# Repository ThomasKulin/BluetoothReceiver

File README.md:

# BluetoothReceiver
TODO:
make this readme not shit

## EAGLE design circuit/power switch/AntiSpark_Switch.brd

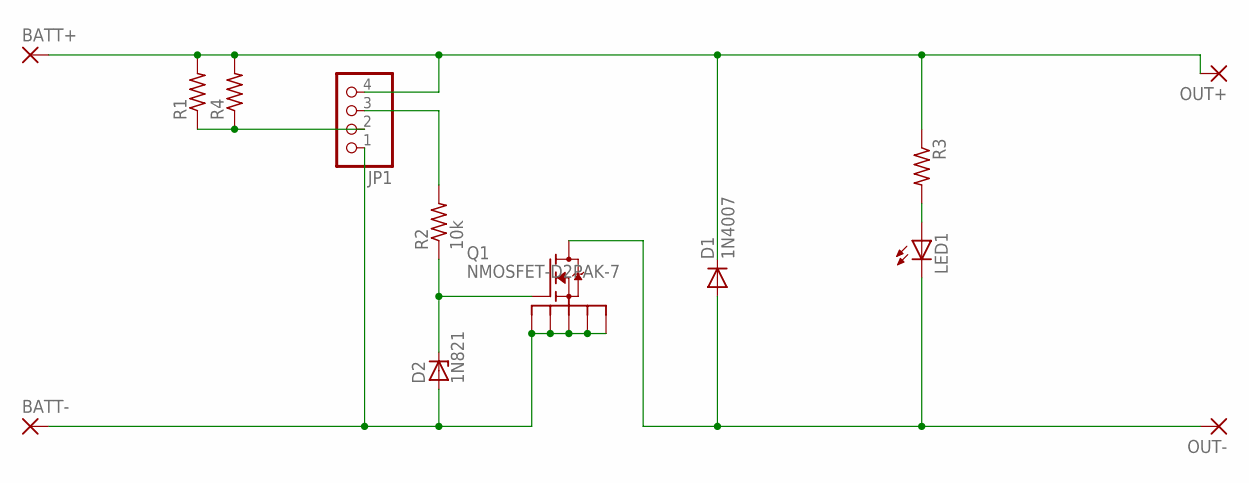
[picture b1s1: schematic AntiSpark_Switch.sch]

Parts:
BATT+: WIREPAD4,16O1,6; 4,16O1,6
BATT-: WIREPAD4,16O1,6; 4,16O1,6
D1: 1N4007; DO41-10
D2: 1N821; DO35Z10
JP1: PINHD-1X4; 1X04
LED1: LED5MM
OUT+: WIREPAD4,16O1,6; 4,16O1,6
OUT-: WIREPAD4,16O1,6; 4,16O1,6
Q1: NMOSFET-D2PAK-7; D2PAK-7
R1, R3, R4: R-US_0207/7; 0207/7
R2: 10k; 0207/7

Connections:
unnamed: BATT-.1, D2.A, JP1.1, Q1.S1, Q1.S2, Q1.S3, Q1.S4, Q1.S5
unnamed: D2.C, Q1.G, R2.1
unnamed: JP1.3, R2.2
unnamed: BATT+.1, D1.C, JP1.4, OUT+.1, R1.2, R3.1, R4.2
unnamed: D1.A, LED1.K (C), OUT-.1, Q1.D
unnamed: JP1.2, R1.1, R4.1
unnamed: LED1.A, R3.2

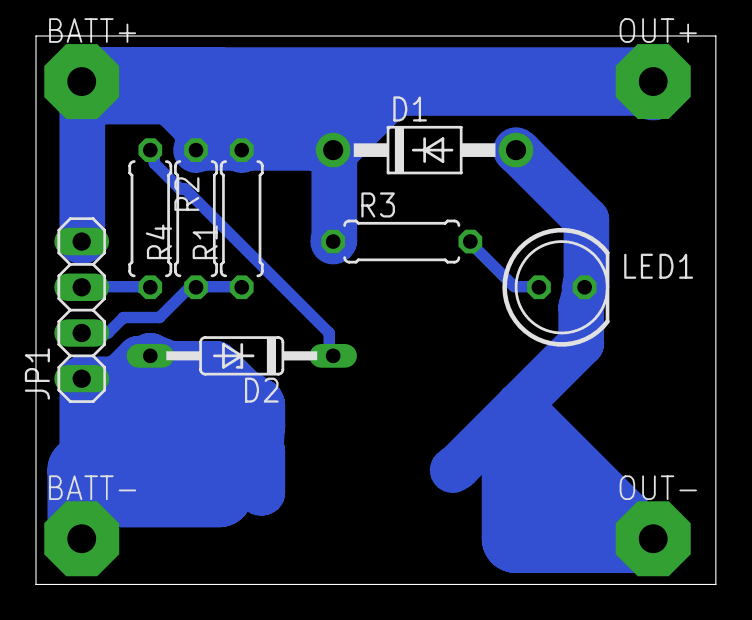
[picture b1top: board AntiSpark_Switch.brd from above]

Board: 2 copper layers, 37.8 x 30.5 mm, 13 parts (1 on the bottom side), 7 nets.

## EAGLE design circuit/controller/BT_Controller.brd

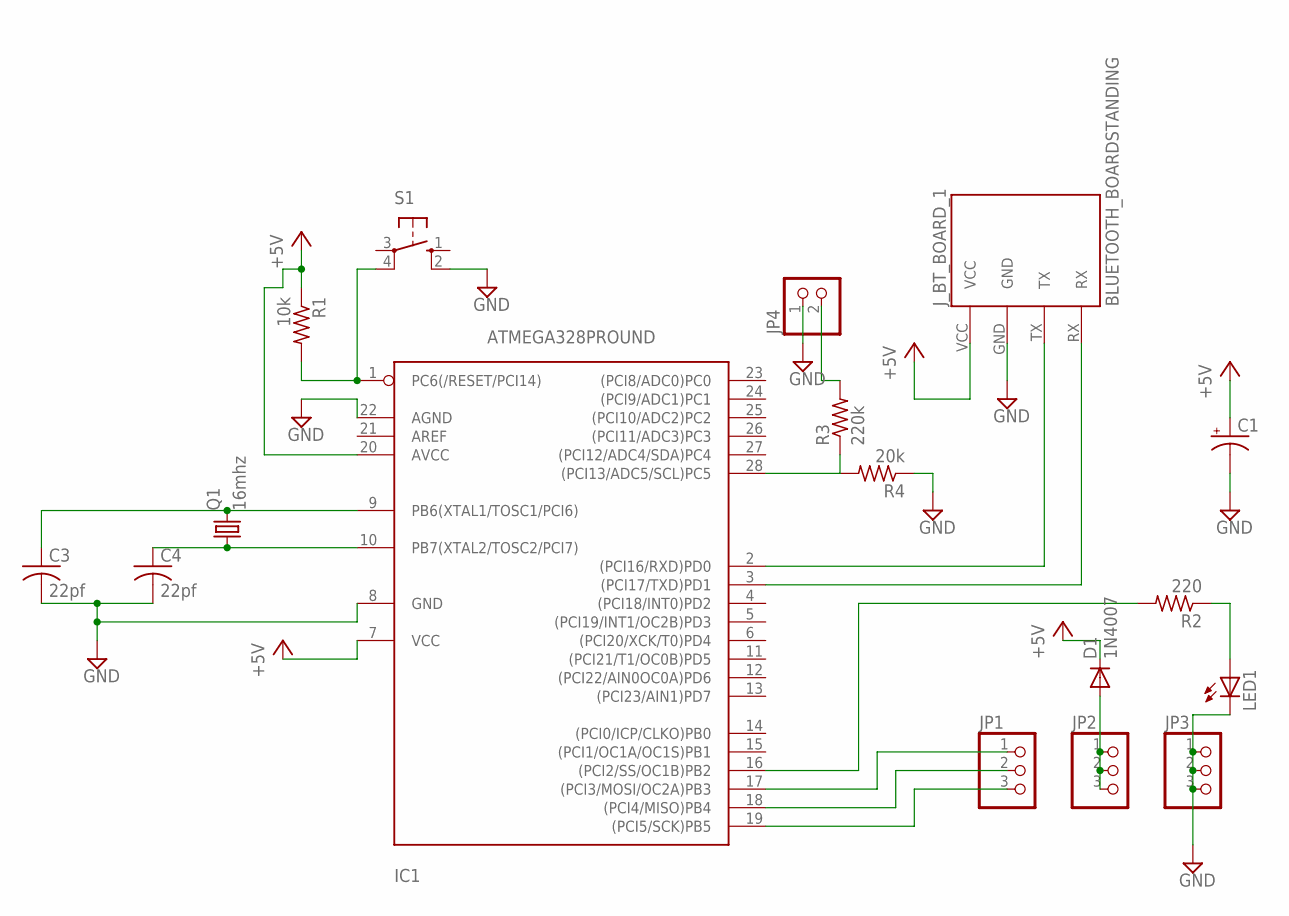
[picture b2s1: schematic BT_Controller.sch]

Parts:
C1: CPOL-USE2,5-6E; E2,5-6E
C3, C4: 22pf; C050-024X044
D1: 1N4007; DO41-10
IC1: ATMEGA328PROUND; DIL28-3-ROUND
JP1, JP2, JP3: PINHD-1X3; 1X03
JP4: PINHD-1X2; 1X02
J_BT_BOARD_1: BLUETOOTH_BOARDSTANDING; BT_BOARD_FOOTPRINT_STANDING
LED1: LED5MM
Q1: 16mhz; HC49U70
R1: 10k; 0207/7
R2: 220; 0207/7
R3: 220k; 0207/7
R4: 20k; 0207/7
S1: 10-XX; B3F-10XX

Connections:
+5V: C1.+, D1.C, IC1.7 (VCC), IC1.20 (AVCC), J_BT_BOARD_1.VCC, R1.1
GND: C1.-, C3.2, C4.2, IC1.8 (GND), IC1.22 (AGND), JP3.1, JP3.2, JP3.3, JP4.1, J_BT_BOARD_1.GND, LED1.K (C), R4.1, S1.2 (S1)
unnamed: C3.1, IC1.9 (PB6(XTAL1/TOSC1/PCI6)), Q1.2
unnamed: C4.1, IC1.10 (PB7(XTAL2/TOSC2/PCI7)), Q1.1
unnamed: D1.A, JP2.1, JP2.2, JP2.3
unnamed: IC1.1 (PC6(/RESET/PCI14)), R1.2, S1.4 (P1)
unnamed: IC1.16 ((PCI2/SS/OC1B)PB2), R2.2
unnamed: LED1.A, R2.1
unnamed: IC1.17 ((PCI3/MOSI/OC2A)PB3), JP1.1
unnamed: IC1.18 ((PCI4/MISO)PB4), JP1.2
unnamed: IC1.19 ((PCI5/SCK)PB5), JP1.3
unnamed: IC1.2 ((PCI16/RXD)PD0), J_BT_BOARD_1.TX
unnamed: IC1.3 ((PCI17/TXD)PD1), J_BT_BOARD_1.RX
unnamed: IC1.28 ((PCI13/ADC5/SCL)PC5), R3.1, R4.2
unnamed: JP4.2, R3.2

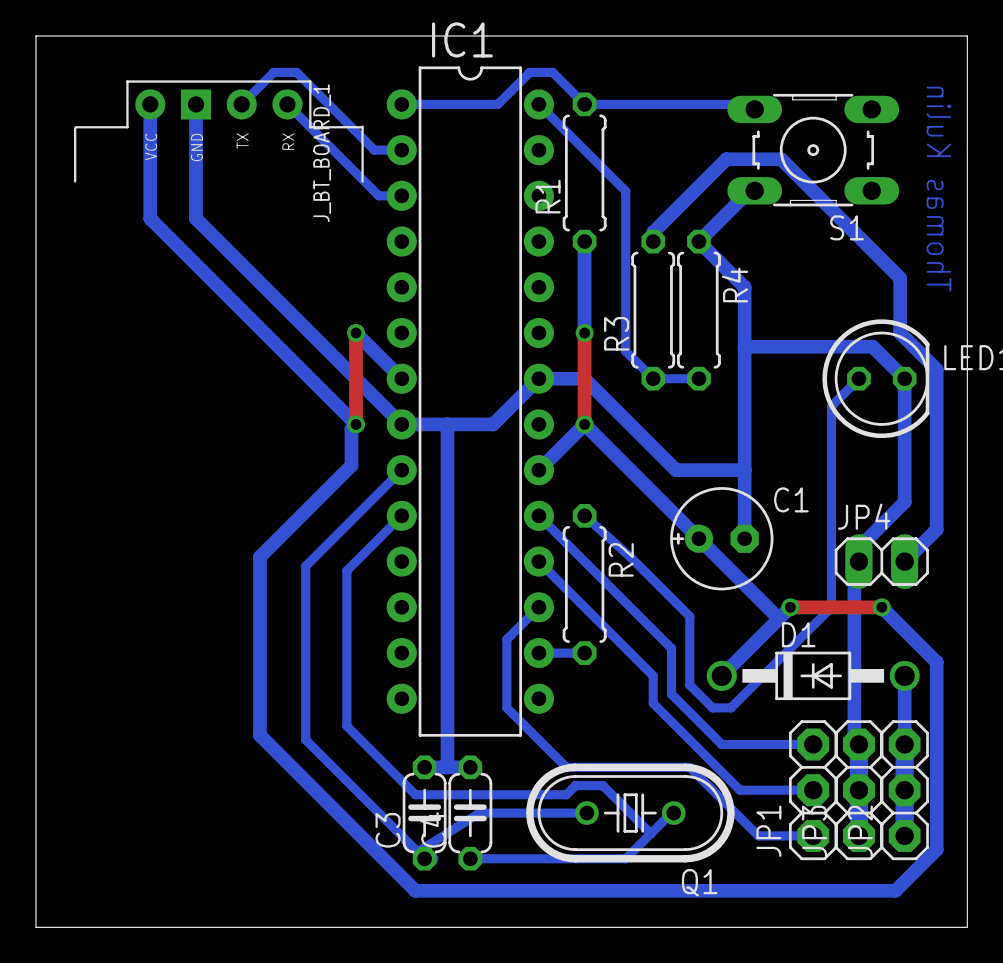
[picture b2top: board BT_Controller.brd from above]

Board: 2 copper layers, 51.7 x 49.5 mm, 17 parts (0 on the bottom side), 15 nets.

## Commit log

2018-03-10 Controller Files
2018-03-11 test
2018-03-11 added schematics and board laouts for the controller and power switch circuitry
